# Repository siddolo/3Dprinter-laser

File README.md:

# 3D printer laser adapter

This circuit needs to adapt a PWM/TTL laser module to a 3D printer using a cooling fan output.
You need to use a laser which has the PWM/TTL control on a port different from the one used for the power.

You can turn the laser ON with GCODE command `M106 Sxxx` (where `xxx` is an integer number from 0 and 255) and the laser OFF with `M107`

For example:
```
M106 S127 ; This line turns the laser ON to half power (50%)
M106 S255 ; This line turns the laser ON to full power (100%)
M107 ; This line turns the laser OFF
M106 S0 ; This line turns the laser OFF too (0%)
```

Through the use of JP1 jumper you can switch from Laser to Fan, so you don't need to detach this interface to use your printer normally.

# 12V or 24V printer

If your FAN runs at 24V R1 must be 2.2KOhm, if it runs at 12V R1 must be 1.1KOhm.

Note that JST (white) connectors are rotated to respect Creality 3D Ender 3 PRO polarity, so if your printer has inverted polarity rotate the JST connectors accordingly.

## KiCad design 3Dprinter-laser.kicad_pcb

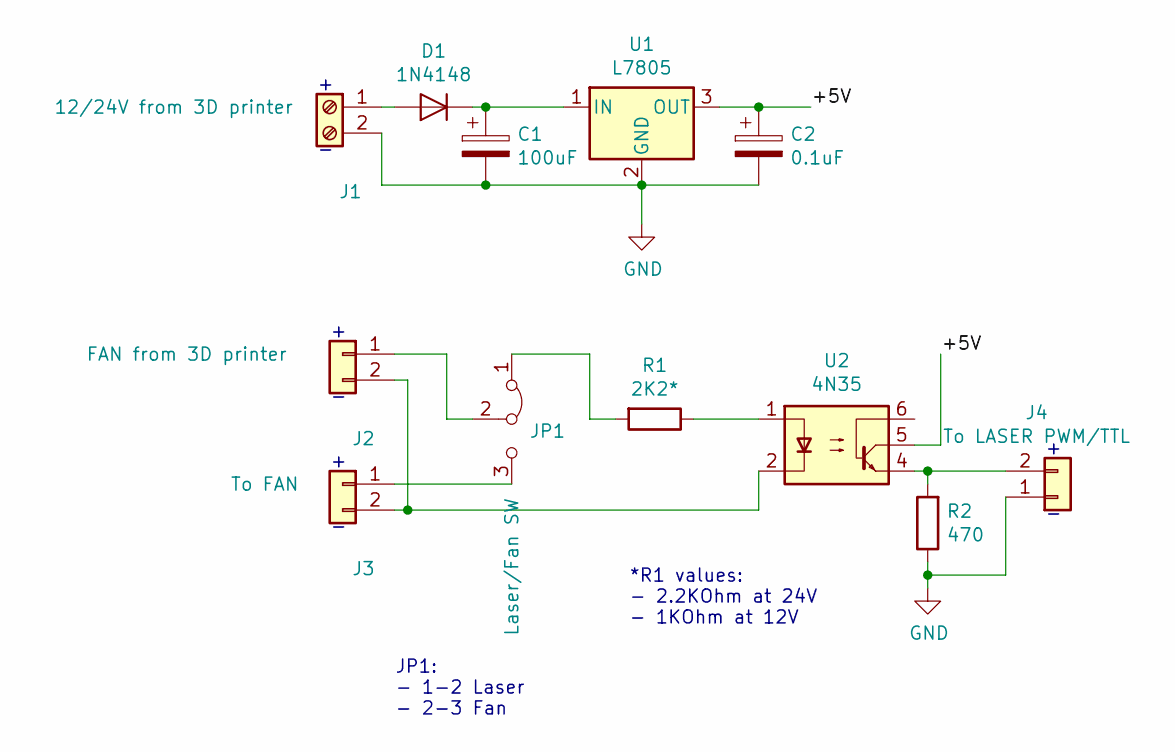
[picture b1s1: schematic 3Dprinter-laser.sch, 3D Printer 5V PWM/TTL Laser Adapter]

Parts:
C1: 100uF; CP_Radial_D8.0mm_P3.50mm
C2: 0.1uF; CP_Radial_D5.0mm_P2.00mm
D1: 1N4148; D_DO-34_SOD68_P7.62mm_Horizontal
J1: 12/24V from 3D printer; PhoenixContact_MSTBA_2,5_2-G_1x02_P5.00mm_Horizontal
J2: FAN from 3D printer; JST_XH_B02B-XH-A_1x02_P2.50mm_Vertical
J3: To FAN; JST_XH_B02B-XH-A_1x02_P2.50mm_Vertical
J4: To LASER PWM/TTL; JST_XH_B02B-XH-A_1x02_P2.50mm_Vertical
JP1: Laser/Fan SW; PinHeader_1x03_P2.54mm_Vertical
R1: 2K2*; R_Axial_DIN0207_L6.3mm_D2.5mm_P7.62mm_Horizontal
R2: 470; R_Axial_DIN0207_L6.3mm_D2.5mm_P7.62mm_Horizontal
U1: L7805; TO-92_Inline
U2: 4N35; DIP-6_W7.62mm

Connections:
/+5V: C2.1, U1.3 (OUT), U2.5
GND: C1.2, C2.2, J1.2, J4.1, R2.1, U1.2 (GND)
unnamed: C1.1, D1.1 (K), U1.1 (IN)
unnamed: D1.2 (A), J1.1
unnamed: J2.1, JP1.2 (C)
unnamed: J2.2, J3.2, U2.2
unnamed: J3.1, JP1.3 (B)
unnamed: J4.2, R2.2, U2.4
unnamed: JP1.1 (A), R1.2
unnamed: R1.1, U2.1

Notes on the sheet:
*R1 values: - 2.2KOhm at 24V - 1KOhm at 12V
JP1: - 1-2 Laser - 2-3 Fan

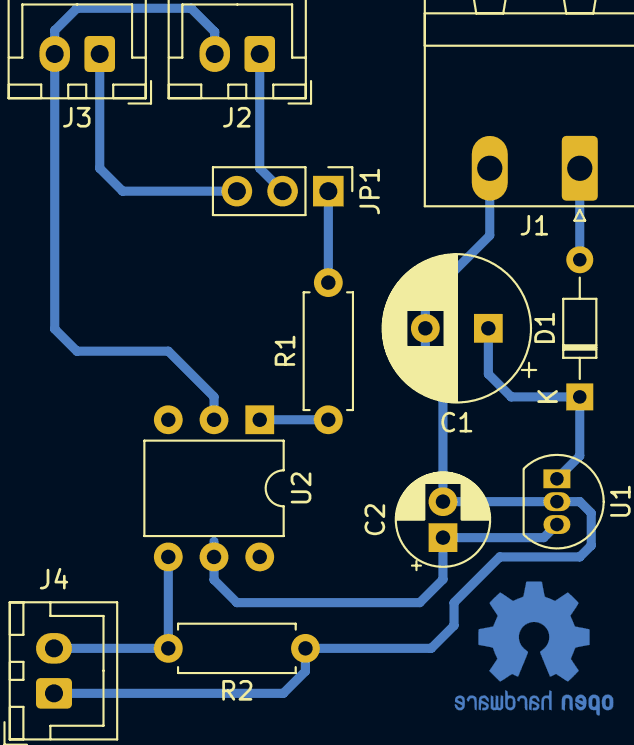
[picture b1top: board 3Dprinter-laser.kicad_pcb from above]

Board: 2 copper layers, 12 parts (0 on the bottom side), 10 nets.

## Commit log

2019-02-16 3D printer laser adapter
2020-01-15 readme update
2021-01-28 fix JP1
2021-01-28 fix png
2023-12-22 Ko-fi
